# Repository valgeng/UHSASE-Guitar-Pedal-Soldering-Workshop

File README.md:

# 🎸 UH SASE Guitar Pedal Soldering Workshop

Welcome and thank you for coming to the **UH SASE Guitar Pedal Soldering Workshop**! Follow these pages during the event to learn how a digital delay pedal works, practice soldering, explore a custom PCB, and personalize a pedal design.

> **Before the event:** Our organizers will confirm the soldering demonstration video, materials, assembly instructions, and how to etch. The provided electronics files below are just design references. 

## 📚 Workshop guide

| Step | Guide | What you'll learn |
| --- | --- | --- |
| 01 | [Introduction](guide/01-introduction.md) | What a guitar pedal does and what delay sounds like |
| 02 | [Pedal controls](guide/02-pedal-controls.md) | Time, feedback, volume |
| 03 | [How the pedal works](guide/03-how-it-works.md) | How a signal works to create altered sound |
| 04 | [Soldering tutorial](guide/04-soldering-guide.md) | Safety, soldering steps, and demonstration video |
| 05 | [Pedal assembly](guide/05-assembly-guide.md) | Guided PCB assembly |
| 06 | [Etching activity](guide/06-etching.md) | Customize your pedal with Po the Panda |

[Workshop presentation (PDF)](presentation/Guitar-Pedal-Soldering-Workshop.pdf) — reference slides.

## 🔧 PCB files used 

- [KiCad schematic](files/delay_pedal_teensy.kicad_sch) — electronic connections.
- [KiCad PCB layout](files/delay_pedal_teensy.kicad_pcb) — physical board layout and copper routing.
- [Gerber manufacturing ZIP](files/gerbers_delay_pedal_teensy.zip) — PCB fabrication outputs.
  
## 🛠 Workshop flow

1. Learn what a guitar pedal is and the controls we are focusing on today. 
2. Practice soldering with leds.
3. Practice ethcing.
4. When ready, begin soldering the PCB **only with an instructor present!**
5. Assemble the PCB
6. Test the pedal with a guitar and amplifier!.

## ⚠️ Safety precautions

A hot soldering iron can cause burns; use gloves, goggles and fume extractor. 

**Questions?** Ask a UH SASE workshop organizer.

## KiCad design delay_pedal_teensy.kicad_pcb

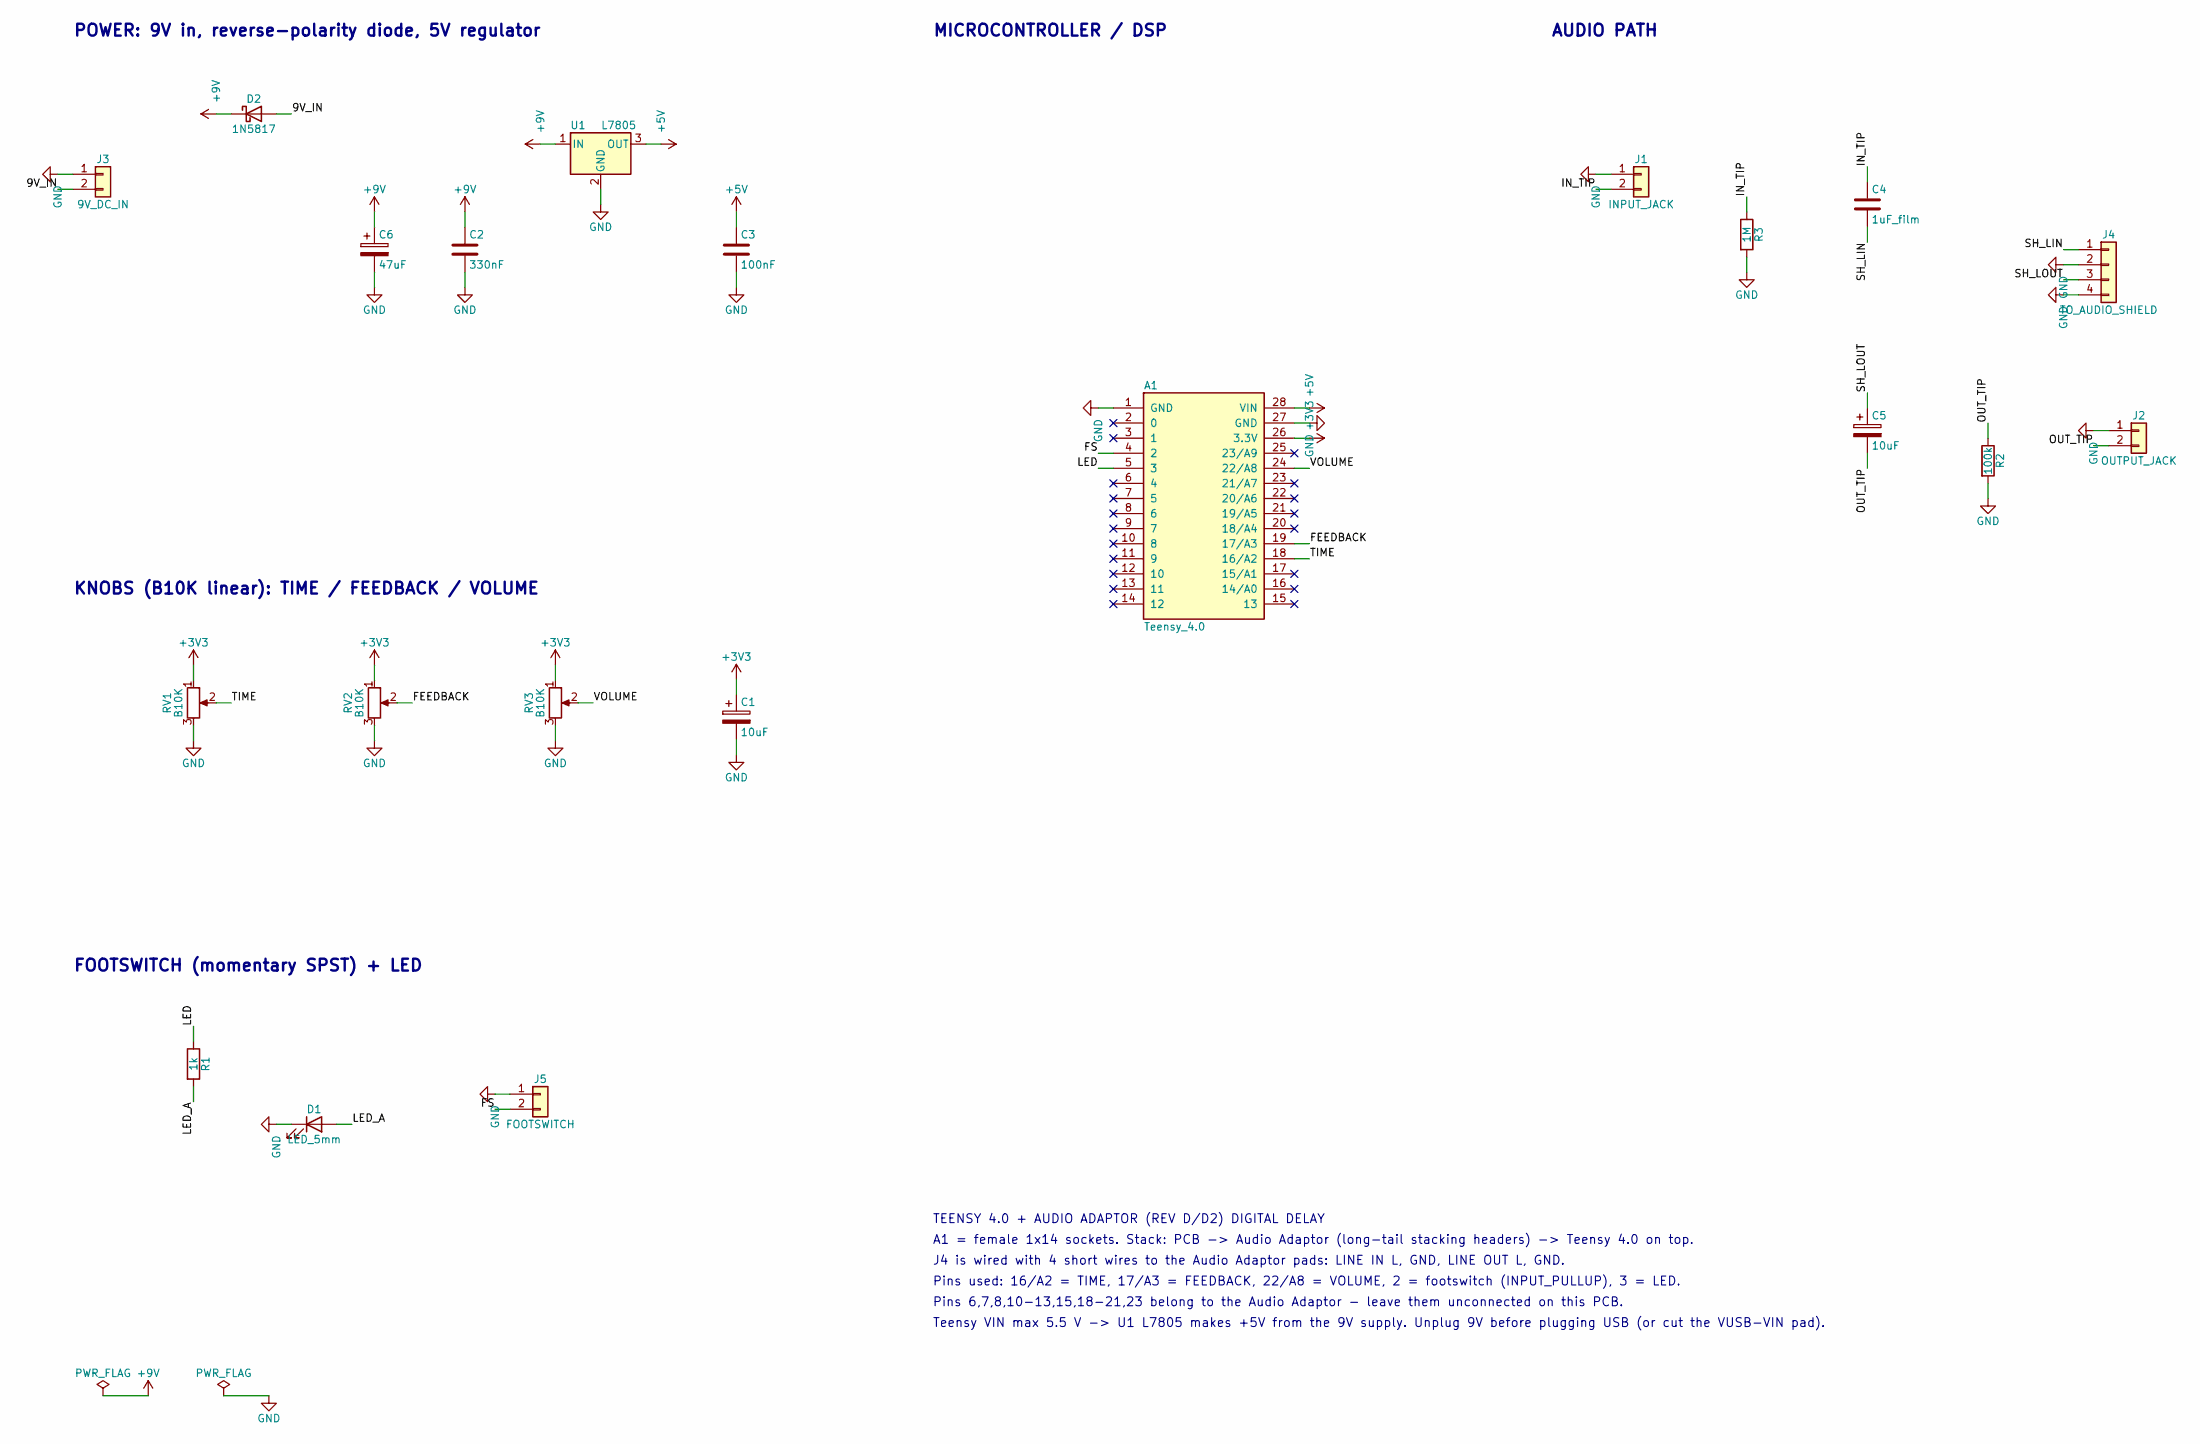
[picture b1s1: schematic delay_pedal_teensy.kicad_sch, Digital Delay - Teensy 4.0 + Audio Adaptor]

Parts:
A1: Teensy_4.0; Teensy_4.0_Socket
C1, C5: 10uF; CP_Radial_D5.0mm_P2.00mm
C2: 330nF; C_Disc_D5.0mm_W2.5mm_P2.50mm
C3: 100nF; C_Disc_D5.0mm_W2.5mm_P2.50mm
C4: 1uF_film; C_Rect_L7.2mm_W3.5mm_P5.00mm_FKS2_FKP2_MKS2_MKP2
C6: 47uF; CP_Radial_D5.0mm_P2.00mm
D1: LED_5mm; LED_D5.0mm
D2: 1N5817; D_DO-41_SOD81_P7.62mm_Horizontal
J1: INPUT_JACK; SolderWire-0.5sqmm_1x02_P4.6mm_D0.9mm_OD2.1mm
J2: OUTPUT_JACK; SolderWire-0.5sqmm_1x02_P4.6mm_D0.9mm_OD2.1mm
J3: 9V_DC_IN; SolderWire-0.5sqmm_1x02_P4.6mm_D0.9mm_OD2.1mm
J4: TO_AUDIO_SHIELD; PinHeader_1x04_P2.54mm_Vertical
J5: FOOTSWITCH; SolderWire-0.5sqmm_1x02_P4.6mm_D0.9mm_OD2.1mm
R1: 1k; R_Axial_DIN0207_L6.3mm_D2.5mm_P7.62mm_Horizontal
R2: 100k; R_Axial_DIN0207_L6.3mm_D2.5mm_P7.62mm_Horizontal
R3: 1M; R_Axial_DIN0207_L6.3mm_D2.5mm_P7.62mm_Horizontal
RV1, RV2, RV3: B10K; RV16AF-41
U1: L7805; TO-220-3_Vertical

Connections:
+3V3: A1.26 (3.3V), C1.1, RV1.1, RV2.1, RV3.1
+5V: A1.28 (VIN), C3.1, U1.3 (OUT)
+9V: C2.1, C6.1, D2.1 (K), U1.1 (IN)
/9V_IN: D2.2 (A), J3.2
/FEEDBACK: A1.19 (17/A3), RV2.2
/FS: A1.4 (2), J5.2
/IN_TIP: C4.1, J1.2, R3.1
/LED: A1.5 (3), R1.1
/LED_A: D1.2 (A), R1.2
/OUT_TIP: C5.2, J2.2, R2.1
/SH_LIN: C4.2, J4.1
/SH_LOUT: C5.1, J4.3
/TIME: A1.18 (16/A2), RV1.2
/VOLUME: A1.24 (22/A8), RV3.2
GND: A1.1 (GND), A1.27 (GND), C1.2, C2.2, C3.2, C6.2, D1.1 (K), J1.1, J2.1, J3.1, J4.2, J4.4, J5.1, R2.2, R3.2, RV1.3, RV2.3, RV3.3, U1.2 (GND)

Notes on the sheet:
POWER: 9V in, reverse-polarity diode, 5V regulator
KNOBS (B10K linear): TIME / FEEDBACK / VOLUME
FOOTSWITCH (momentary SPST) + LED
MICROCONTROLLER / DSP
AUDIO PATH
TEENSY 4.0 + AUDIO ADAPTOR (REV D/D2) DIGITAL DELAY
A1 = female 1x14 sockets. Stack: PCB -> Audio Adaptor (long-tail stacking headers) -> Teensy 4.0 on top.
J4 is wired with 4 short wires to the Audio Adaptor pads: LINE IN L, GND, LINE OUT L, GND.
Pins used: 16/A2 = TIME, 17/A3 = FEEDBACK, 22/A8 = VOLUME, 2 = footswitch (INPUT_PULLUP), 3 = LED.
Pins 6,7,8,10-13,15,18-21,23 belong to the Audio Adaptor - leave them unconnected on this PCB.
Teensy VIN max 5.5 V -> U1 L7805 makes +5V from the 9V supply. Unplug 9V before plugging USB (or cut the VUSB-VIN pad).

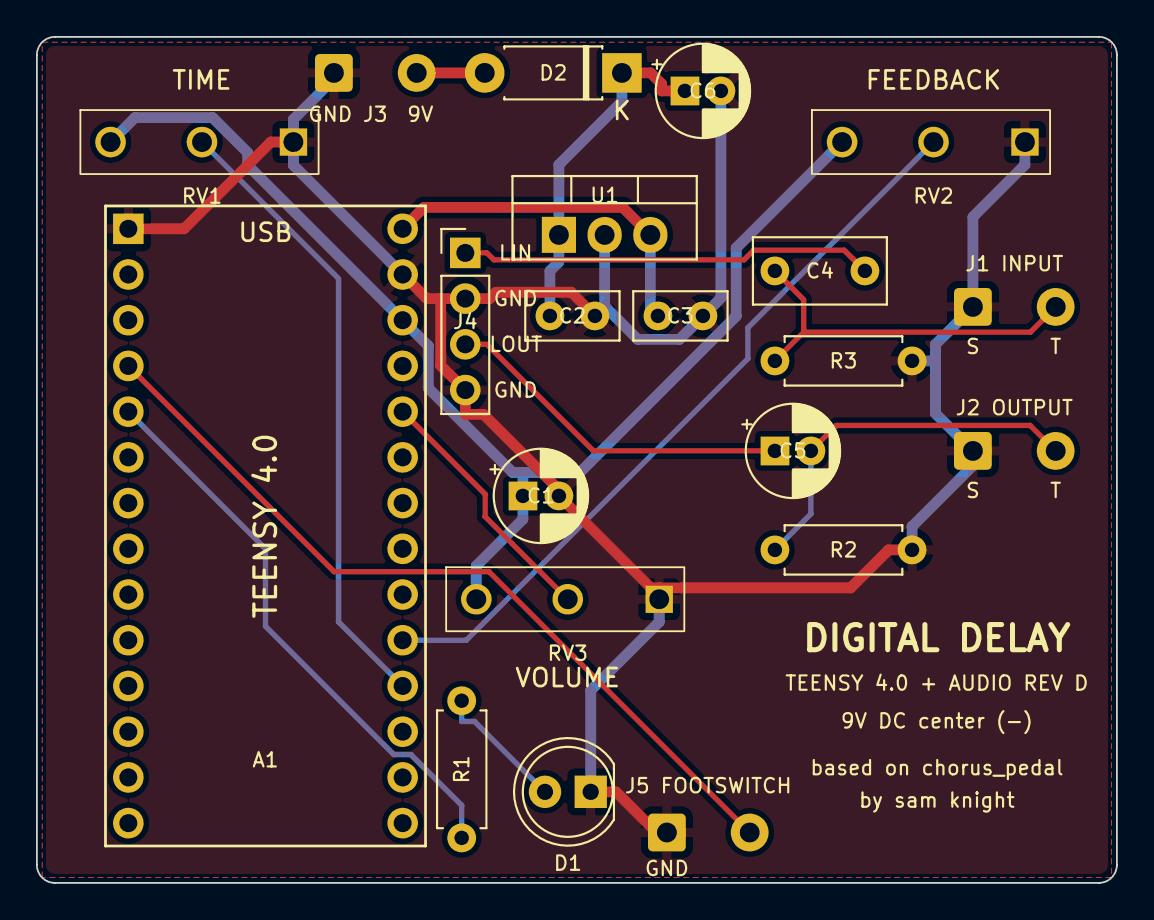
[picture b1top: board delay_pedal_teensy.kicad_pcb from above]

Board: 2 copper layers, 60.0 x 47.0 mm, 21 parts (0 on the bottom side), 15 nets.
